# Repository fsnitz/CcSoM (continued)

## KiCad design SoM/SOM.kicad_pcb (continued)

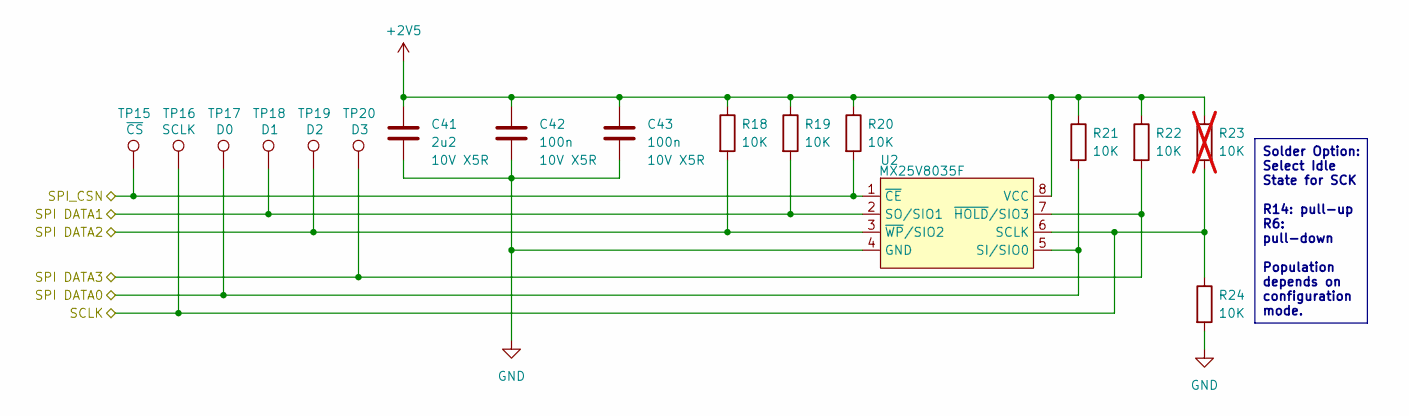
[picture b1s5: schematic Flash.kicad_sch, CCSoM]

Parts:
C41: 2u2; C_0402_1005Metric; Voltage/Precision 10V X5R; Mouser Part Number GRM155Z71A225KE44D
C42, C43: 100n; C_0402_1005Metric; Voltage/Precision 10V X5R; Mouser Part Number GRM155R71C104KA88J
R18, R19, R20, R21, R22, R24: 10K; R_0402_1005Metric; Mouser Part Number MCS0402MC1002FE000
R23: 10K; R_0402_1005Metric; Mouser Part Number 71-CRCW0201-10K; not fitted
TP15: ~{CS}; TestPoint_Pad_D1.0mm
TP16: SCLK; TestPoint_Pad_D1.0mm
TP17: D0; TestPoint_Pad_D1.0mm
TP18: D1; TestPoint_Pad_D1.0mm
TP19: D2; TestPoint_Pad_D1.0mm
TP20: D3; TestPoint_Pad_D1.0mm
U2: MX25V8035F; SOP-8(150_200MIL); Mouser Part Number MX25V8035FM2I

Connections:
+2V5: C41.1, C42.1, C43.1, R18.1, R19.1, R20.1, R21.1, R22.1, R23.1, U2.8 (VCC); also elsewhere on the board
/FPGA_Top_Module/Flash/SCLK: R23.2, R24.1, TP16.1, U2.6 (SCLK); also elsewhere on the board
/FPGA_Top_Module/Flash/SPI DATA0: R21.2, TP17.1, U2.5 (SI/SIO0); also elsewhere on the board
/FPGA_Top_Module/Flash/SPI DATA1: R19.2, TP18.1, U2.2 (SO/SIO1); also elsewhere on the board
/FPGA_Top_Module/Flash/SPI DATA2: R18.2, TP19.1, U2.3 (~WP/SIO2); also elsewhere on the board
/FPGA_Top_Module/Flash/SPI DATA3: R22.2, TP20.1, U2.7 (~HOLD/SIO3); also elsewhere on the board
/FPGA_Top_Module/Flash/SPI_CSN: R20.2, TP15.1, U2.1 (~CE); also elsewhere on the board
GND: C41.2, C42.2, C43.2, R24.2, U2.4 (GND); also elsewhere on the board

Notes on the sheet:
Solder Option: Select Idle State for SCK R14: pull-up R6: pull-down Population depends on configuration mode.

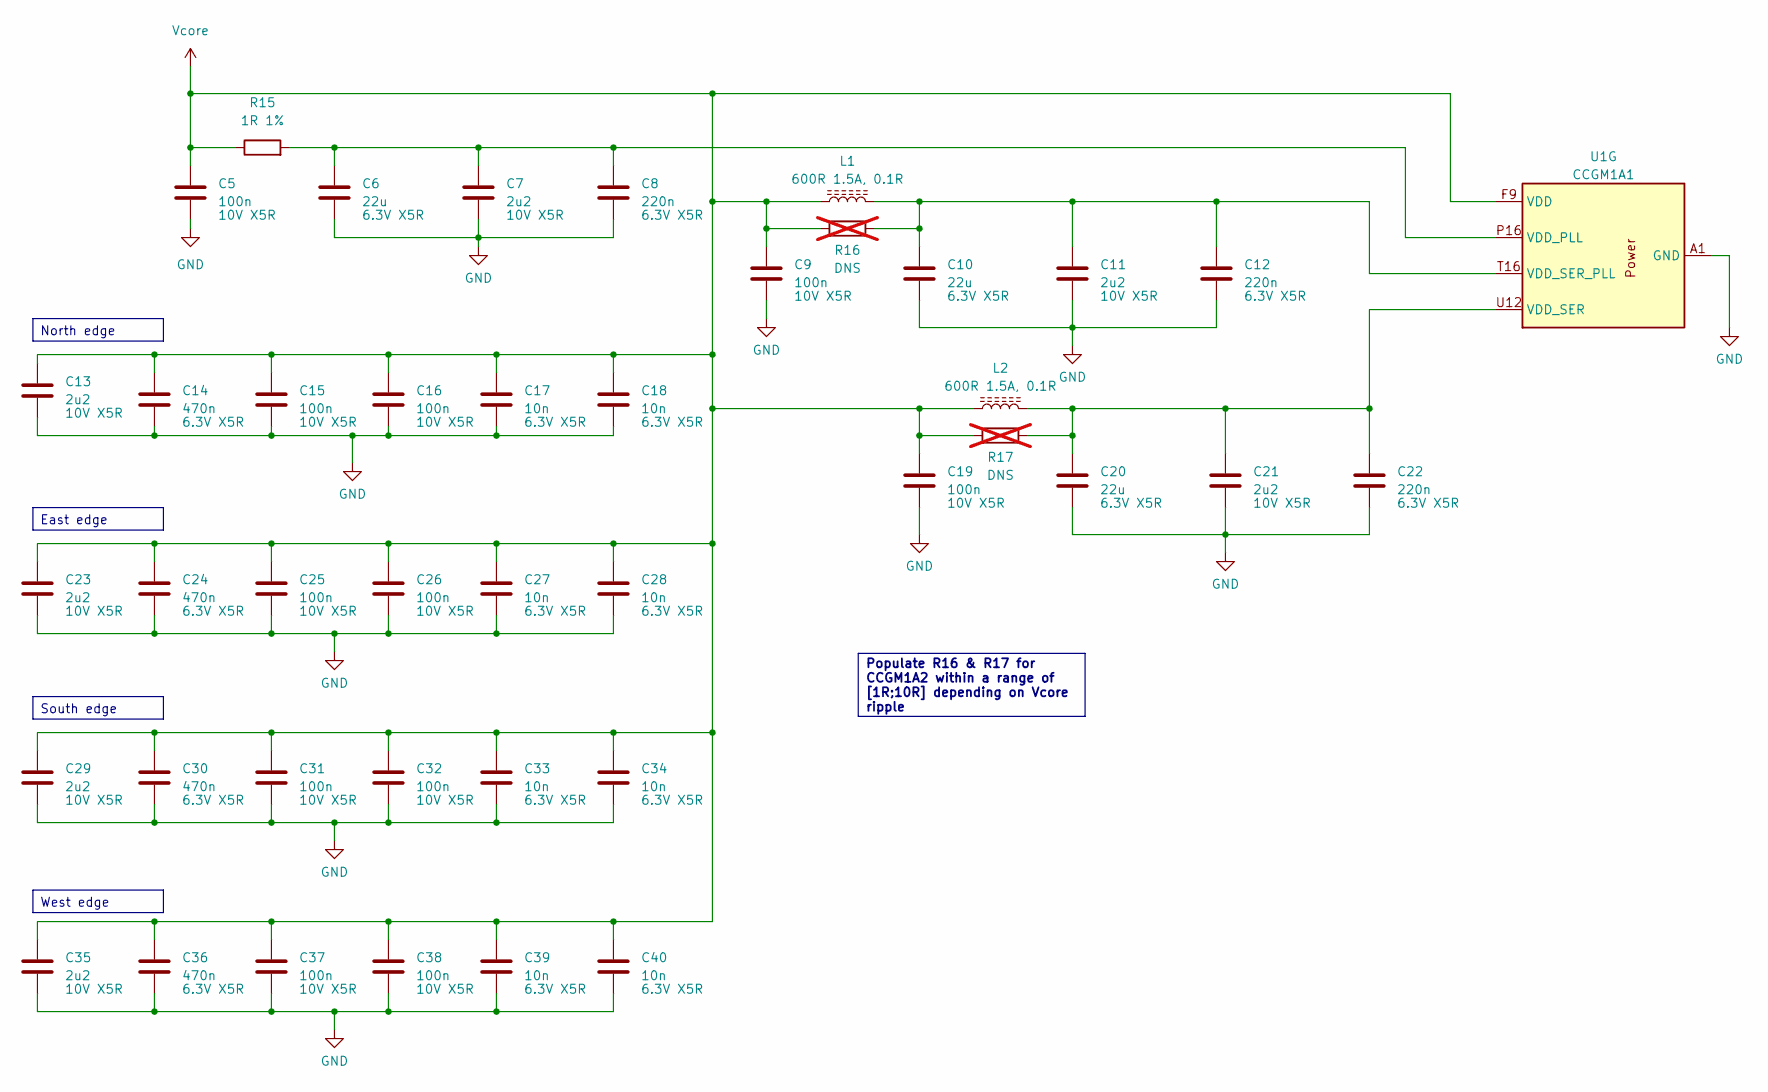
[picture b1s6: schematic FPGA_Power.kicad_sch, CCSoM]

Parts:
C5, C9, C15, C16, C19, C25, C26, C31, C32, C37, C38: 100n; C_0402_1005Metric; Voltage/Precision 10V X5R; Mouser Part Number GRM155R71C104KA88J
C6, C10, C20: 22u; C_0603_1608Metric; Voltage/Precision 6.3V X5R; Mouser Part Number GRM188C61C226ME01W
C7, C11, C13, C21, C23, C29, C35: 2u2; C_0402_1005Metric; Voltage/Precision 10V X5R; Mouser Part Number GRM155Z71A225KE44D
C8, C12, C22: 220n; C_0402_1005Metric; Voltage/Precision 6.3V X5R; Mouser Part Number GRM155R71C224KA12D
C14, C24, C30, C36: 470n; C_0402_1005Metric; Voltage/Precision 6.3V X5R; Mouser Part Number GRT155C81C474KE01D
C17, C18, C27, C28, C33, C34, C39, C40: 10n; C_0402_1005Metric; Voltage/Precision 6.3V X5R; Mouser Part Number GRM155R71C103KA01D
L1, L2: 600R 1.5A, 0.1R; C_0603_1608Metric; Mouser Part Number 74269262601
R15: 1R 1%; R_0402_1005Metric; Mouser Part Number CRCW04021R00FKEDHP
R16, R17: DNS; R_0402_1005Metric; Mouser Part Number 71-CRCW020133R0FNED; not fitted
U1: CCGM1A1; BGA-324_15.0x15.0mm_Layout18x18_P0.8mm_Ball0.45mm_Pad0.4mm_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; Mouser Part Number CCGM1A1-BGA324

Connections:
GND: C5.2, C6.2, C7.2, C8.2, C9.2, C10.2, C11.2, C12.2, C13.2, C14.2, C15.2, C16.2, C17.2, C18.2, C19.2, C20.2, C21.2, C22.2, C23.2, C24.2, C25.2, C26.2, C27.2, C28.2, C29.2, C30.2, C31.2, C32.2, C33.2, C34.2, C35.2, C36.2, C37.2, C38.2, C39.2, C40.2, U1.A1 (GND), U1.A7 (GND), U1.A10 (GND), U1.A13 (GND), U1.A18 (GND), U1.B16 (GND), U1.C1 (GND), U1.E5 (GND), U1.E7 (GND), U1.E9 (GND), U1.E11 (GND), U1.E13 (GND), U1.E18 (GND), U1.F1 (GND), U1.F6 (GND), U1.F8 (GND), U1.F10 (GND), U1.F12 (GND), U1.F14 (GND), U1.G5 (GND), U1.G7 (GND), U1.G9 (GND), U1.G11 (GND), U1.G13 (GND), U1.H6 (GND), U1.H8 (GND), U1.H10 (GND), U1.H12 (GND), U1.H14 (GND), U1.H18 (GND), U1.J1 (GND), U1.J5 (GND), U1.J7 (GND), U1.J9 (GND), U1.J11 (GND), U1.J13 (GND), U1.K6 (GND), U1.K8 (GND), U1.K10 (GND), U1.K12 (GND), U1.K14 (GND), U1.L5 (GND), U1.L7 (GND), U1.L9 (GND), U1.L11 (GND), U1.L13 (GND), U1.L18 (GND), U1.M1 (GND), U1.M6 (GND), U1.M8 (GND), U1.M10 (GND), U1.M12 (GND), U1.M16 (GND), U1.N7 (GND), U1.N9 (GND), U1.N12 (GND), U1.N17 (GND), U1.P4 (GND), U1.P7 (GND), U1.P9 (GND), U1.R12 (GND), U1.R16 (GND), U1.T4 (GND), U1.T11 (GND), U1.T17 (GND), U1.U15 (GND), U1.V1 (GND), U1.V6 (GND), U1.V9 (GND), U1.V18 (GND); also elsewhere on the board
unnamed: C20.1, C21.1, C22.1, L2.2, R17.1, U1.U12 (VDD_SER), U1.V17 (VDD_SER)
unnamed: C6.1, C7.1, C8.1, R15.2, U1.P16 (VDD_PLL)
unnamed: C10.1, C11.1, C12.1, L1.2, R16.1, U1.T16 (VDD_SER_PLL)
Vcore: C5.1, C9.1, C13.1, C14.1, C15.1, C16.1, C17.1, C18.1, C19.1, C23.1, C24.1, C25.1, C26.1, C27.1, C28.1, C29.1, C30.1, C31.1, C32.1, C33.1, C34.1, C35.1, C36.1, C37.1, C38.1, C39.1, C40.1, L1.1, L2.1, R15.1, R16.2, R17.2, U1.F9 (VDD), U1.G6 (VDD), U1.G8 (VDD), U1.G10 (VDD), U1.G12 (VDD), U1.H7 (VDD), U1.H9 (VDD), U1.H11 (VDD), U1.H13 (VDD), U1.J6 (VDD), U1.J8 (VDD), U1.J10 (VDD), U1.J12 (VDD), U1.K7 (VDD), U1.K9 (VDD), U1.K11 (VDD), U1.K13 (VDD), U1.L6 (VDD), U1.L8 (VDD), U1.L10 (VDD), U1.L12 (VDD), U1.M7 (VDD), U1.M9 (VDD), U1.M11 (VDD), U1.M13 (VDD), U1.N6 (VDD), U1.N8 (VDD), U1.N10 (VDD); also elsewhere on the board

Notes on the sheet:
East edge
North edge
South edge
Populate R16 & R17 for CCGM1A2 within a range of [1R;10R] depending on Vcore ripple
West edge

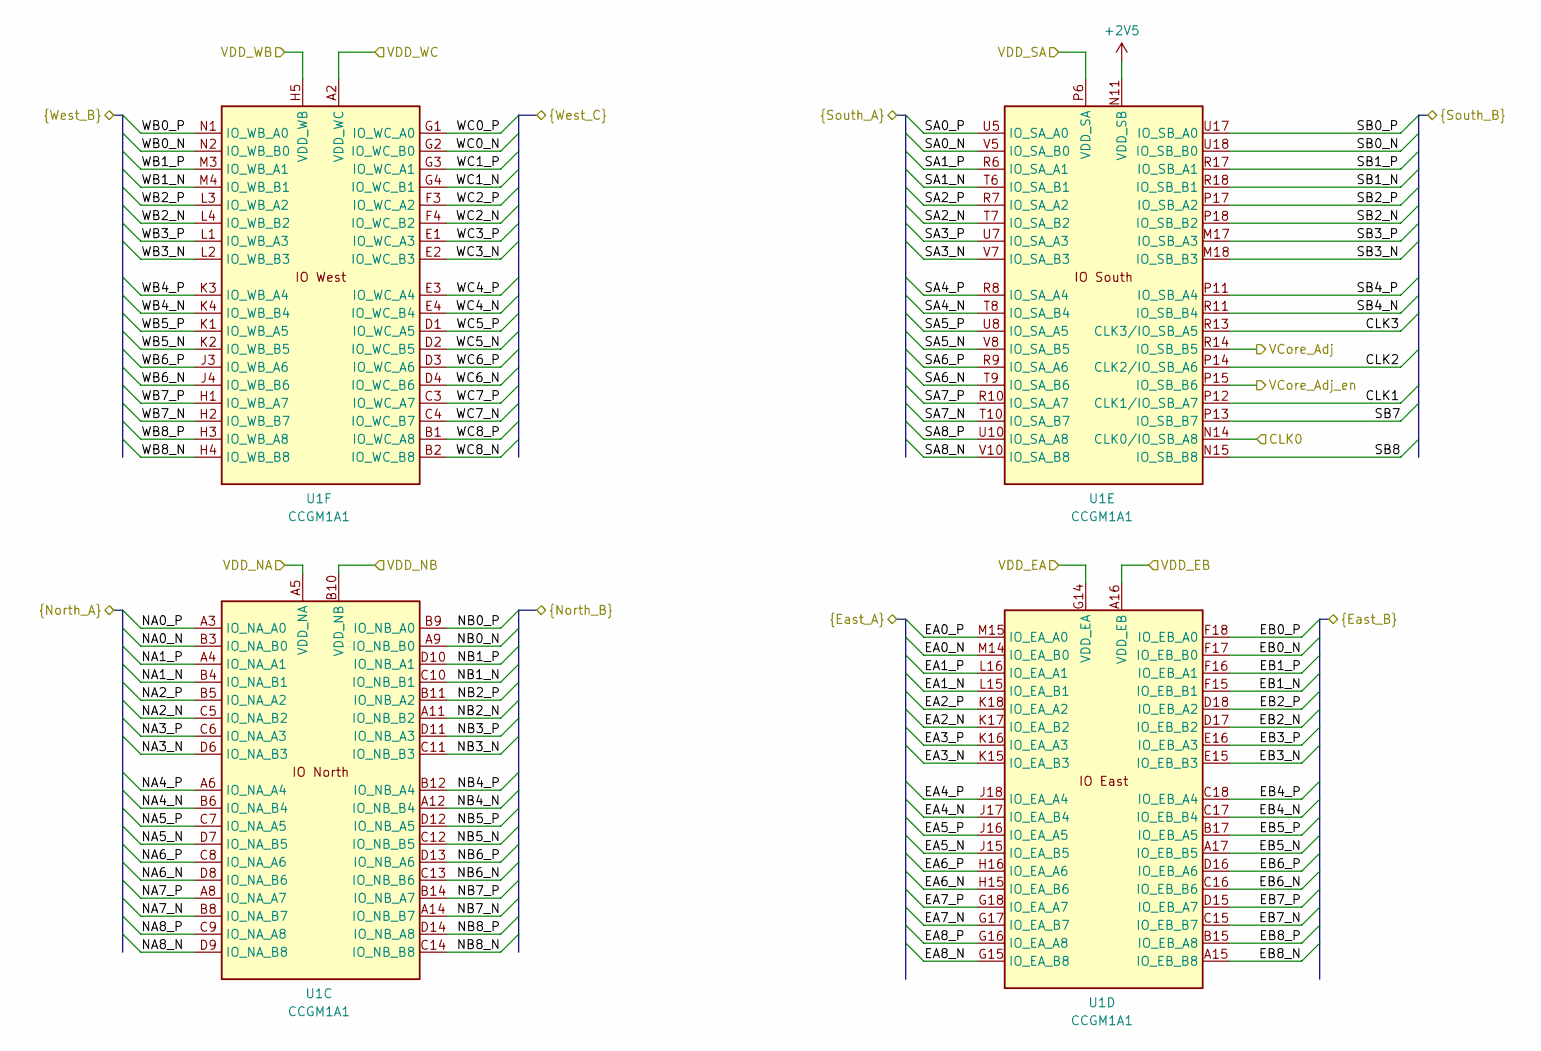
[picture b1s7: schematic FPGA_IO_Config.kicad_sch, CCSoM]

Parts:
U1: CCGM1A1; BGA-324_15.0x15.0mm_Layout18x18_P0.8mm_Ball0.45mm_Pad0.4mm_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; Mouser Part Number CCGM1A1-BGA324

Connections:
+2V5: U1.N11 (VDD_SB), U1.N13 (VDD_SB), U1.N18 (VDD_SB), U1.R15 (VDD_SB), U1.T18 (VDD_SB); also elsewhere on the board
/FPGA_Top_Module/CLK0: U1.N14 (CLK0/IO_SB_A8); also elsewhere on the board
/FPGA_Top_Module/CLK1: U1.P12 (CLK1/IO_SB_A7); also elsewhere on the board
/FPGA_Top_Module/CLK2: U1.P14 (CLK2/IO_SB_A6); also elsewhere on the board
/FPGA_Top_Module/CLK3: U1.R13 (CLK3/IO_SB_A5); also elsewhere on the board
/FPGA_Top_Module/EA0_N: U1.M14 (IO_EA_B0); also elsewhere on the board
/FPGA_Top_Module/EA0_P: U1.M15 (IO_EA_A0); also elsewhere on the board
/FPGA_Top_Module/EA1_N: U1.L15 (IO_EA_B1); also elsewhere on the board
/FPGA_Top_Module/EA1_P: U1.L16 (IO_EA_A1); also elsewhere on the board
/FPGA_Top_Module/EA2_N: U1.K17 (IO_EA_B2); also elsewhere on the board
/FPGA_Top_Module/EA2_P: U1.K18 (IO_EA_A2); also elsewhere on the board
/FPGA_Top_Module/EA3_N: U1.K15 (IO_EA_B3); also elsewhere on the board
/FPGA_Top_Module/EA3_P: U1.K16 (IO_EA_A3); also elsewhere on the board
/FPGA_Top_Module/EA4_N: U1.J17 (IO_EA_B4); also elsewhere on the board
/FPGA_Top_Module/EA4_P: U1.J18 (IO_EA_A4); also elsewhere on the board
/FPGA_Top_Module/EA5_N: U1.J15 (IO_EA_B5); also elsewhere on the board
/FPGA_Top_Module/EA5_P: U1.J16 (IO_EA_A5); also elsewhere on the board
/FPGA_Top_Module/EA6_N: U1.H15 (IO_EA_B6); also elsewhere on the board
/FPGA_Top_Module/EA6_P: U1.H16 (IO_EA_A6); also elsewhere on the board
/FPGA_Top_Module/EA7_N: U1.G17 (IO_EA_B7); also elsewhere on the board
/FPGA_Top_Module/EA7_P: U1.G18 (IO_EA_A7); also elsewhere on the board
/FPGA_Top_Module/EA8_N: U1.G15 (IO_EA_B8); also elsewhere on the board
/FPGA_Top_Module/EA8_P: U1.G16 (IO_EA_A8); also elsewhere on the board
/FPGA_Top_Module/EB0_N: U1.F17 (IO_EB_B0); also elsewhere on the board
/FPGA_Top_Module/EB0_P: U1.F18 (IO_EB_A0); also elsewhere on the board
/FPGA_Top_Module/EB1_N: U1.F15 (IO_EB_B1); also elsewhere on the board
/FPGA_Top_Module/EB1_P: U1.F16 (IO_EB_A1); also elsewhere on the board
/FPGA_Top_Module/EB2_N: U1.D17 (IO_EB_B2); also elsewhere on the board
/FPGA_Top_Module/EB2_P: U1.D18 (IO_EB_A2); also elsewhere on the board
/FPGA_Top_Module/EB3_N: U1.E15 (IO_EB_B3); also elsewhere on the board
/FPGA_Top_Module/EB3_P: U1.E16 (IO_EB_A3); also elsewhere on the board
/FPGA_Top_Module/EB4_N: U1.C17 (IO_EB_B4); also elsewhere on the board
/FPGA_Top_Module/EB4_P: U1.C18 (IO_EB_A4); also elsewhere on the board
/FPGA_Top_Module/EB5_N: U1.A17 (IO_EB_B5); also elsewhere on the board
/FPGA_Top_Module/EB5_P: U1.B17 (IO_EB_A5); also elsewhere on the board
/FPGA_Top_Module/EB6_N: U1.C16 (IO_EB_B6); also elsewhere on the board
/FPGA_Top_Module/EB6_P: U1.D16 (IO_EB_A6); also elsewhere on the board
/FPGA_Top_Module/EB7_N: U1.C15 (IO_EB_B7); also elsewhere on the board
/FPGA_Top_Module/EB7_P: U1.D15 (IO_EB_A7); also elsewhere on the board
/FPGA_Top_Module/EB8_N: U1.A15 (IO_EB_B8); also elsewhere on the board
/FPGA_Top_Module/EB8_P: U1.B15 (IO_EB_A8); also elsewhere on the board
/FPGA_Top_Module/FPGA_IO_Config/VDD_EA: U1.G14 (VDD_EA), U1.H17 (VDD_EA), U1.J14 (VDD_EA), U1.L14 (VDD_EA), U1.L17 (VDD_EA); also elsewhere on the board
/FPGA_Top_Module/FPGA_IO_Config/VDD_EB: U1.A16 (VDD_EB), U1.B18 (VDD_EB), U1.E14 (VDD_EB), U1.E17 (VDD_EB), U1.F13 (VDD_EB); also elsewhere on the board
/FPGA_Top_Module/FPGA_IO_Config/VDD_NA: U1.A5 (VDD_NA), U1.B7 (VDD_NA), U1.E6 (VDD_NA), U1.E8 (VDD_NA), U1.F7 (VDD_NA); also elsewhere on the board
/FPGA_Top_Module/FPGA_IO_Config/VDD_NB: U1.B10 (VDD_NB), U1.B13 (VDD_NB), U1.E10 (VDD_NB), U1.E12 (VDD_NB), U1.F11 (VDD_NB); also elsewhere on the board
/FPGA_Top_Module/FPGA_IO_Config/VDD_SA: U1.P6 (VDD_SA), U1.P8 (VDD_SA), U1.P10 (VDD_SA), U1.U6 (VDD_SA), U1.U9 (VDD_SA); also elsewhere on the board
/FPGA_Top_Module/FPGA_IO_Config/VDD_WB: U1.H5 (VDD_WB), U1.J2 (VDD_WB), U1.K5 (VDD_WB), U1.M2 (VDD_WB), U1.M5 (VDD_WB); also elsewhere on the board
/FPGA_Top_Module/FPGA_IO_Config/VDD_WC: U1.A2 (VDD_WC), U1.C2 (VDD_WC), U1.D5 (VDD_WC), U1.F2 (VDD_WC), U1.F5 (VDD_WC); also elsewhere on the board
/FPGA_Top_Module/NA0_N: U1.B3 (IO_NA_B0); also elsewhere on the board
/FPGA_Top_Module/NA0_P: U1.A3 (IO_NA_A0); also elsewhere on the board
/FPGA_Top_Module/NA1_N: U1.B4 (IO_NA_B1); also elsewhere on the board
/FPGA_Top_Module/NA1_P: U1.A4 (IO_NA_A1); also elsewhere on the board
/FPGA_Top_Module/NA2_N: U1.C5 (IO_NA_B2); also elsewhere on the board
/FPGA_Top_Module/NA2_P: U1.B5 (IO_NA_A2); also elsewhere on the board
/FPGA_Top_Module/NA3_N: U1.D6 (IO_NA_B3); also elsewhere on the board
/FPGA_Top_Module/NA3_P: U1.C6 (IO_NA_A3); also elsewhere on the board
/FPGA_Top_Module/NA4_N: U1.B6 (IO_NA_B4); also elsewhere on the board
/FPGA_Top_Module/NA4_P: U1.A6 (IO_NA_A4); also elsewhere on the board
/FPGA_Top_Module/NA5_N: U1.D7 (IO_NA_B5); also elsewhere on the board
/FPGA_Top_Module/NA5_P: U1.C7 (IO_NA_A5); also elsewhere on the board
/FPGA_Top_Module/NA6_N: U1.D8 (IO_NA_B6); also elsewhere on the board
/FPGA_Top_Module/NA6_P: U1.C8 (IO_NA_A6); also elsewhere on the board
/FPGA_Top_Module/NA7_N: U1.B8 (IO_NA_B7); also elsewhere on the board
/FPGA_Top_Module/NA7_P: U1.A8 (IO_NA_A7); also elsewhere on the board
/FPGA_Top_Module/NA8_N: U1.D9 (IO_NA_B8); also elsewhere on the board
/FPGA_Top_Module/NA8_P: U1.C9 (IO_NA_A8); also elsewhere on the board
/FPGA_Top_Module/NB0_N: U1.A9 (IO_NB_B0); also elsewhere on the board
/FPGA_Top_Module/NB0_P: U1.B9 (IO_NB_A0); also elsewhere on the board
/FPGA_Top_Module/NB1_N: U1.C10 (IO_NB_B1); also elsewhere on the board
/FPGA_Top_Module/NB1_P: U1.D10 (IO_NB_A1); also elsewhere on the board
/FPGA_Top_Module/NB2_N: U1.A11 (IO_NB_B2); also elsewhere on the board
/FPGA_Top_Module/NB2_P: U1.B11 (IO_NB_A2); also elsewhere on the board
/FPGA_Top_Module/NB3_N: U1.C11 (IO_NB_B3); also elsewhere on the board
/FPGA_Top_Module/NB3_P: U1.D11 (IO_NB_A3); also elsewhere on the board
/FPGA_Top_Module/NB4_N: U1.A12 (IO_NB_B4); also elsewhere on the board
/FPGA_Top_Module/NB4_P: U1.B12 (IO_NB_A4); also elsewhere on the board
/FPGA_Top_Module/NB5_N: U1.C12 (IO_NB_B5); also elsewhere on the board
/FPGA_Top_Module/NB5_P: U1.D12 (IO_NB_A5); also elsewhere on the board
/FPGA_Top_Module/NB6_N: U1.C13 (IO_NB_B6); also elsewhere on the board
/FPGA_Top_Module/NB6_P: U1.D13 (IO_NB_A6); also elsewhere on the board
/FPGA_Top_Module/NB7_N: U1.A14 (IO_NB_B7); also elsewhere on the board
/FPGA_Top_Module/NB7_P: U1.B14 (IO_NB_A7); also elsewhere on the board
/FPGA_Top_Module/NB8_N: U1.C14 (IO_NB_B8); also elsewhere on the board
/FPGA_Top_Module/NB8_P: U1.D14 (IO_NB_A8); also elsewhere on the board
/FPGA_Top_Module/SA0_N: U1.V5 (IO_SA_B0); also elsewhere on the board
/FPGA_Top_Module/SA0_P: U1.U5 (IO_SA_A0); also elsewhere on the board
/FPGA_Top_Module/SA1_N: U1.T6 (IO_SA_B1); also elsewhere on the board
/FPGA_Top_Module/SA1_P: U1.R6 (IO_SA_A1); also elsewhere on the board
/FPGA_Top_Module/SA2_N: U1.T7 (IO_SA_B2); also elsewhere on the board
/FPGA_Top_Module/SA2_P: U1.R7 (IO_SA_A2); also elsewhere on the board
/FPGA_Top_Module/SA3_N: U1.V7 (IO_SA_B3); also elsewhere on the board
/FPGA_Top_Module/SA3_P: U1.U7 (IO_SA_A3); also elsewhere on the board
/FPGA_Top_Module/SA4_N: U1.T8 (IO_SA_B4); also elsewhere on the board
/FPGA_Top_Module/SA4_P: U1.R8 (IO_SA_A4); also elsewhere on the board
/FPGA_Top_Module/SA5_N: U1.V8 (IO_SA_B5); also elsewhere on the board
/FPGA_Top_Module/SA5_P: U1.U8 (IO_SA_A5); also elsewhere on the board
/FPGA_Top_Module/SA6_N: U1.T9 (IO_SA_B6); also elsewhere on the board
/FPGA_Top_Module/SA6_P: U1.R9 (IO_SA_A6); also elsewhere on the board
/FPGA_Top_Module/SA7_N: U1.T10 (IO_SA_B7); also elsewhere on the board
/FPGA_Top_Module/SA7_P: U1.R10 (IO_SA_A7); also elsewhere on the board
/FPGA_Top_Module/SA8_N: U1.V10 (IO_SA_B8); also elsewhere on the board
/FPGA_Top_Module/SA8_P: U1.U10 (IO_SA_A8); also elsewhere on the board
/FPGA_Top_Module/SB0_N: U1.U18 (IO_SB_B0); also elsewhere on the board
/FPGA_Top_Module/SB0_P: U1.U17 (IO_SB_A0); also elsewhere on the board
/FPGA_Top_Module/SB1_N: U1.R18 (IO_SB_B1); also elsewhere on the board
/FPGA_Top_Module/SB1_P: U1.R17 (IO_SB_A1); also elsewhere on the board
/FPGA_Top_Module/SB2_N: U1.P18 (IO_SB_B2); also elsewhere on the board
/FPGA_Top_Module/SB2_P: U1.P17 (IO_SB_A2); also elsewhere on the board
/FPGA_Top_Module/SB3_N: U1.M18 (IO_SB_B3); also elsewhere on the board
/FPGA_Top_Module/SB3_P: U1.M17 (IO_SB_A3); also elsewhere on the board
/FPGA_Top_Module/SB4_N: U1.R11 (IO_SB_B4); also elsewhere on the board
/FPGA_Top_Module/SB4_P: U1.P11 (IO_SB_A4); also elsewhere on the board
/FPGA_Top_Module/SB7: U1.P13 (IO_SB_B7); also elsewhere on the board
/FPGA_Top_Module/SB8: U1.N15 (IO_SB_B8); also elsewhere on the board
/FPGA_Top_Module/VcAdj: U1.R14 (IO_SB_B5); also elsewhere on the board
/FPGA_Top_Module/WB0_N: U1.N2 (IO_WB_B0); also elsewhere on the board
/FPGA_Top_Module/WB0_P: U1.N1 (IO_WB_A0); also elsewhere on the board
/FPGA_Top_Module/WB1_N: U1.M4 (IO_WB_B1); also elsewhere on the board
/FPGA_Top_Module/WB1_P: U1.M3 (IO_WB_A1); also elsewhere on the board
/FPGA_Top_Module/WB2_N: U1.L4 (IO_WB_B2); also elsewhere on the board
/FPGA_Top_Module/WB2_P: U1.L3 (IO_WB_A2); also elsewhere on the board
/FPGA_Top_Module/WB3_N: U1.L2 (IO_WB_B3); also elsewhere on the board
/FPGA_Top_Module/WB3_P: U1.L1 (IO_WB_A3); also elsewhere on the board
/FPGA_Top_Module/WB4_N: U1.K4 (IO_WB_B4); also elsewhere on the board
/FPGA_Top_Module/WB4_P: U1.K3 (IO_WB_A4); also elsewhere on the board
/FPGA_Top_Module/WB5_N: U1.K2 (IO_WB_B5); also elsewhere on the board
/FPGA_Top_Module/WB5_P: U1.K1 (IO_WB_A5); also elsewhere on the board
/FPGA_Top_Module/WB6_N: U1.J4 (IO_WB_B6); also elsewhere on the board
/FPGA_Top_Module/WB6_P: U1.J3 (IO_WB_A6); also elsewhere on the board
/FPGA_Top_Module/WB7_N: U1.H2 (IO_WB_B7); also elsewhere on the board
/FPGA_Top_Module/WB7_P: U1.H1 (IO_WB_A7); also elsewhere on the board
/FPGA_Top_Module/WB8_N: U1.H4 (IO_WB_B8); also elsewhere on the board
/FPGA_Top_Module/WB8_P: U1.H3 (IO_WB_A8); also elsewhere on the board
/FPGA_Top_Module/WC0_N: U1.G2 (IO_WC_B0); also elsewhere on the board
/FPGA_Top_Module/WC0_P: U1.G1 (IO_WC_A0); also elsewhere on the board
/FPGA_Top_Module/WC1_N: U1.G4 (IO_WC_B1); also elsewhere on the board
/FPGA_Top_Module/WC1_P: U1.G3 (IO_WC_A1); also elsewhere on the board
/FPGA_Top_Module/WC2_N: U1.F4 (IO_WC_B2); also elsewhere on the board
/FPGA_Top_Module/WC2_P: U1.F3 (IO_WC_A2); also elsewhere on the board
/FPGA_Top_Module/WC3_N: U1.E2 (IO_WC_B3); also elsewhere on the board
/FPGA_Top_Module/WC3_P: U1.E1 (IO_WC_A3); also elsewhere on the board
/FPGA_Top_Module/WC4_N: U1.E4 (IO_WC_B4); also elsewhere on the board
/FPGA_Top_Module/WC4_P: U1.E3 (IO_WC_A4); also elsewhere on the board
/FPGA_Top_Module/WC5_N: U1.D2 (IO_WC_B5); also elsewhere on the board
/FPGA_Top_Module/WC5_P: U1.D1 (IO_WC_A5); also elsewhere on the board
/FPGA_Top_Module/WC6_N: U1.D4 (IO_WC_B6); also elsewhere on the board
/FPGA_Top_Module/WC6_P: U1.D3 (IO_WC_A6); also elsewhere on the board
/FPGA_Top_Module/WC7_N: U1.C4 (IO_WC_B7); also elsewhere on the board
/FPGA_Top_Module/WC7_P: U1.C3 (IO_WC_A7); also elsewhere on the board
/FPGA_Top_Module/WC8_N: U1.B2 (IO_WC_B8); also elsewhere on the board
/FPGA_Top_Module/WC8_P: U1.B1 (IO_WC_A8); also elsewhere on the board
/FPGA_Top_Module/~VcAen: U1.P15 (IO_SB_B6); also elsewhere on the board

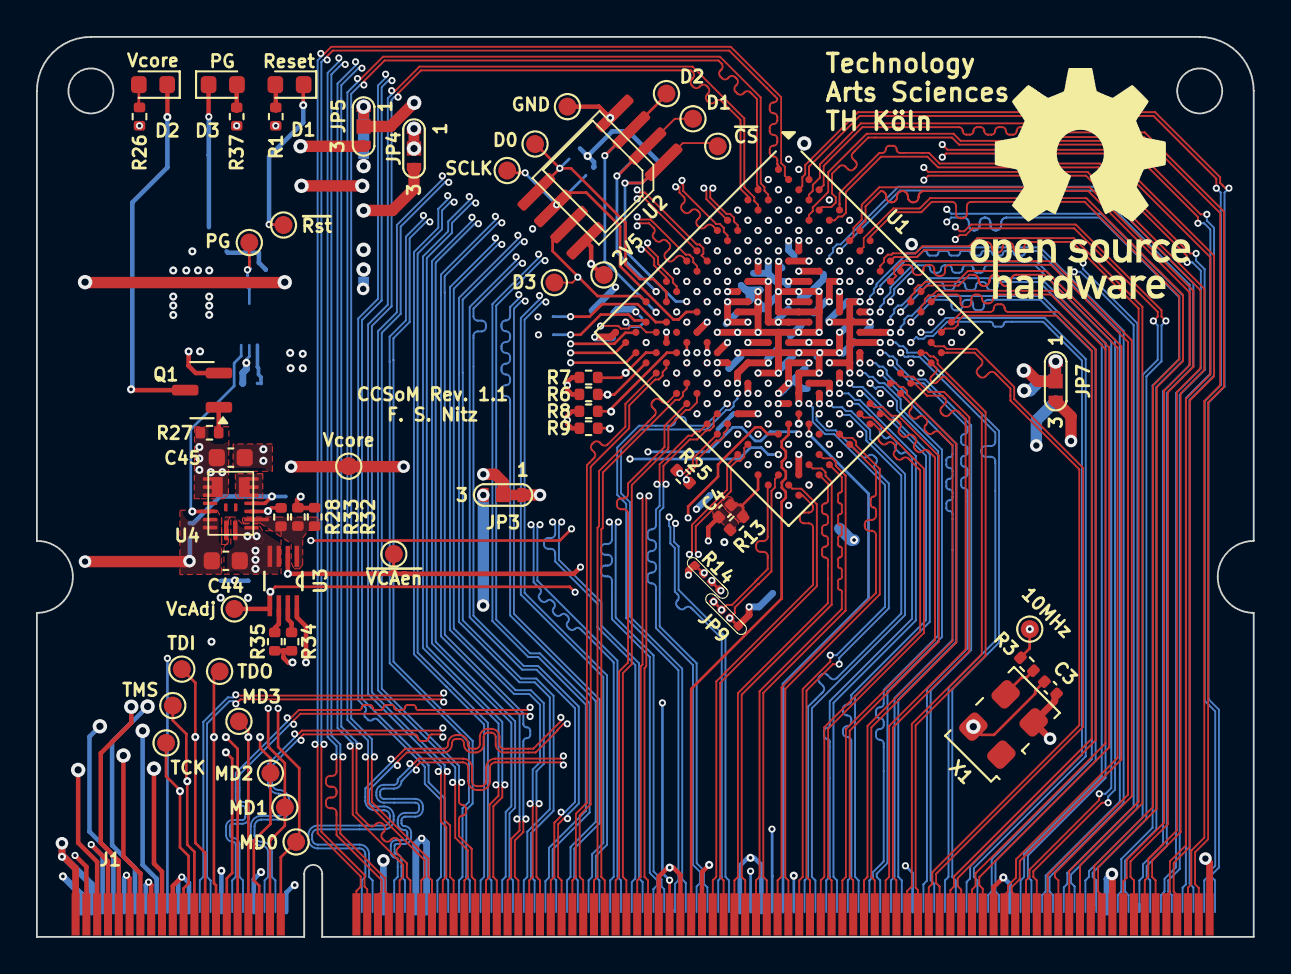
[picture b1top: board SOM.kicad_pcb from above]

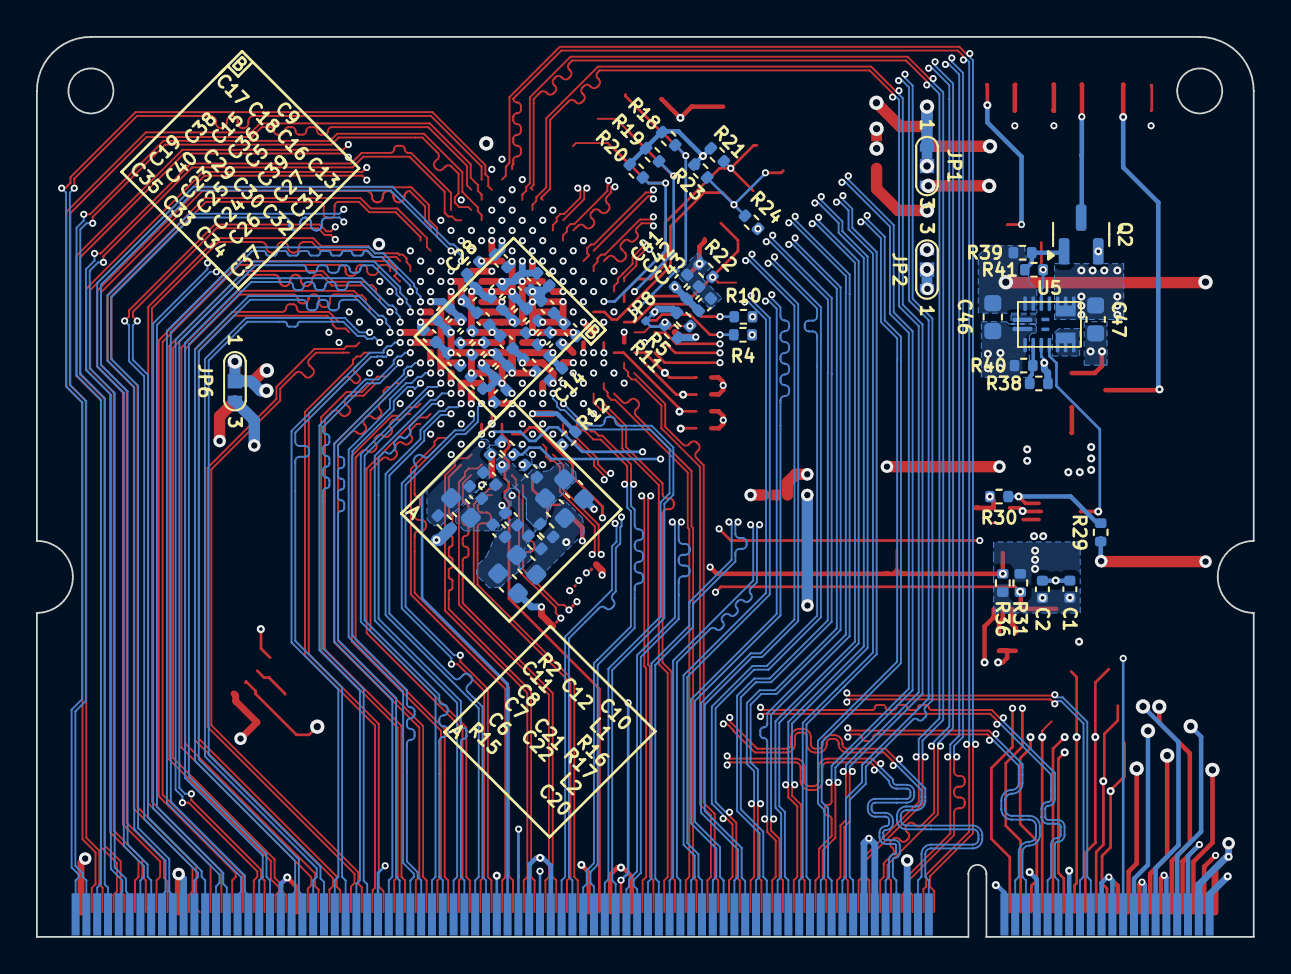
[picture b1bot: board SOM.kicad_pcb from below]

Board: 6 copper layers, 67.6 x 50.0 mm, 135 parts (75 on the bottom side), 212 nets.

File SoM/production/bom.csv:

Designator,Footprint,Quantity,Value,LCSC Part #
"C1, C11, C13, C21, C23, C29, C35, C41, C7",0402,9,2u2,
"C10, C20, C44, C45, C46, C47, C6",0603,7,22u,
"C12, C22, C8",0402,3,220n,
"C14, C24, C30, C36",0402,4,470n,
"C15, C16, C19, C2, C25, C26, C3, C31, C32, C37, C38, C4, C42, C43, C5, C9",0402,16,100n,
"C17, C18, C27, C28, C33, C34, C39, C40",0402,8,10n,
D1,0603,1,Orange,
"D2, D3",0603,2,GREEN,
JP9,Diff_pair_solderbridge_closed,1,~,
"L1, L2",0603,2,"600R 1.5A, 0.1R",
"Q1, Q2",SOT-23,2,BC847,
"R1, R12, R13",0402,3,200R,
"R10, R4, R5",0402,3,4K7,
"R11, R18, R19, R2, R20, R21, R22, R23, R24, R27, R31, R36, R41, R6, R7, R8, R9",0402,17,10K,
R14,Diff_pair_solderbridge_closed,1,100R,
R15,0402,1,1R 1%,
"R16, R17",0402,2,DNS,
R25,0402,1,100R,
"R26, R37",0402,2,1K,
R28,0402,1,20K 1%,
R29,0402,1,100K 1%,
R3,0402,1,33R,
R30,0402,1,51K 1%,
R32,0402,1,240K 1%,
R33,0402,1,47K 1%,
R34,0402,1,120K 1%,
R35,0402,1,62K 1%,
R38,0402,1,200K 1%,
R39,0402,1,12K,
R40,0402,1,63K4 1%,
TP21,TestPoint_Pad_D1.0mm,1,Vcore,
TP22,TestPoint_Pad_D1.0mm,1,PG,
U1,BGA-324_15.0x15.0mm_Layout18x18_P0.8mm_Ball0.45mm_Pad0.4mm_NSMD,1,CCGM1A1,
U2,SOP-8(150_200MIL),1,MX25V8035F,
U3,DCU8,1,74LVC2G53,
"U4, U5",QFN18,2,MPM3833C,
X1,5x3.2_Oscillator,1,ECS-5032MV,

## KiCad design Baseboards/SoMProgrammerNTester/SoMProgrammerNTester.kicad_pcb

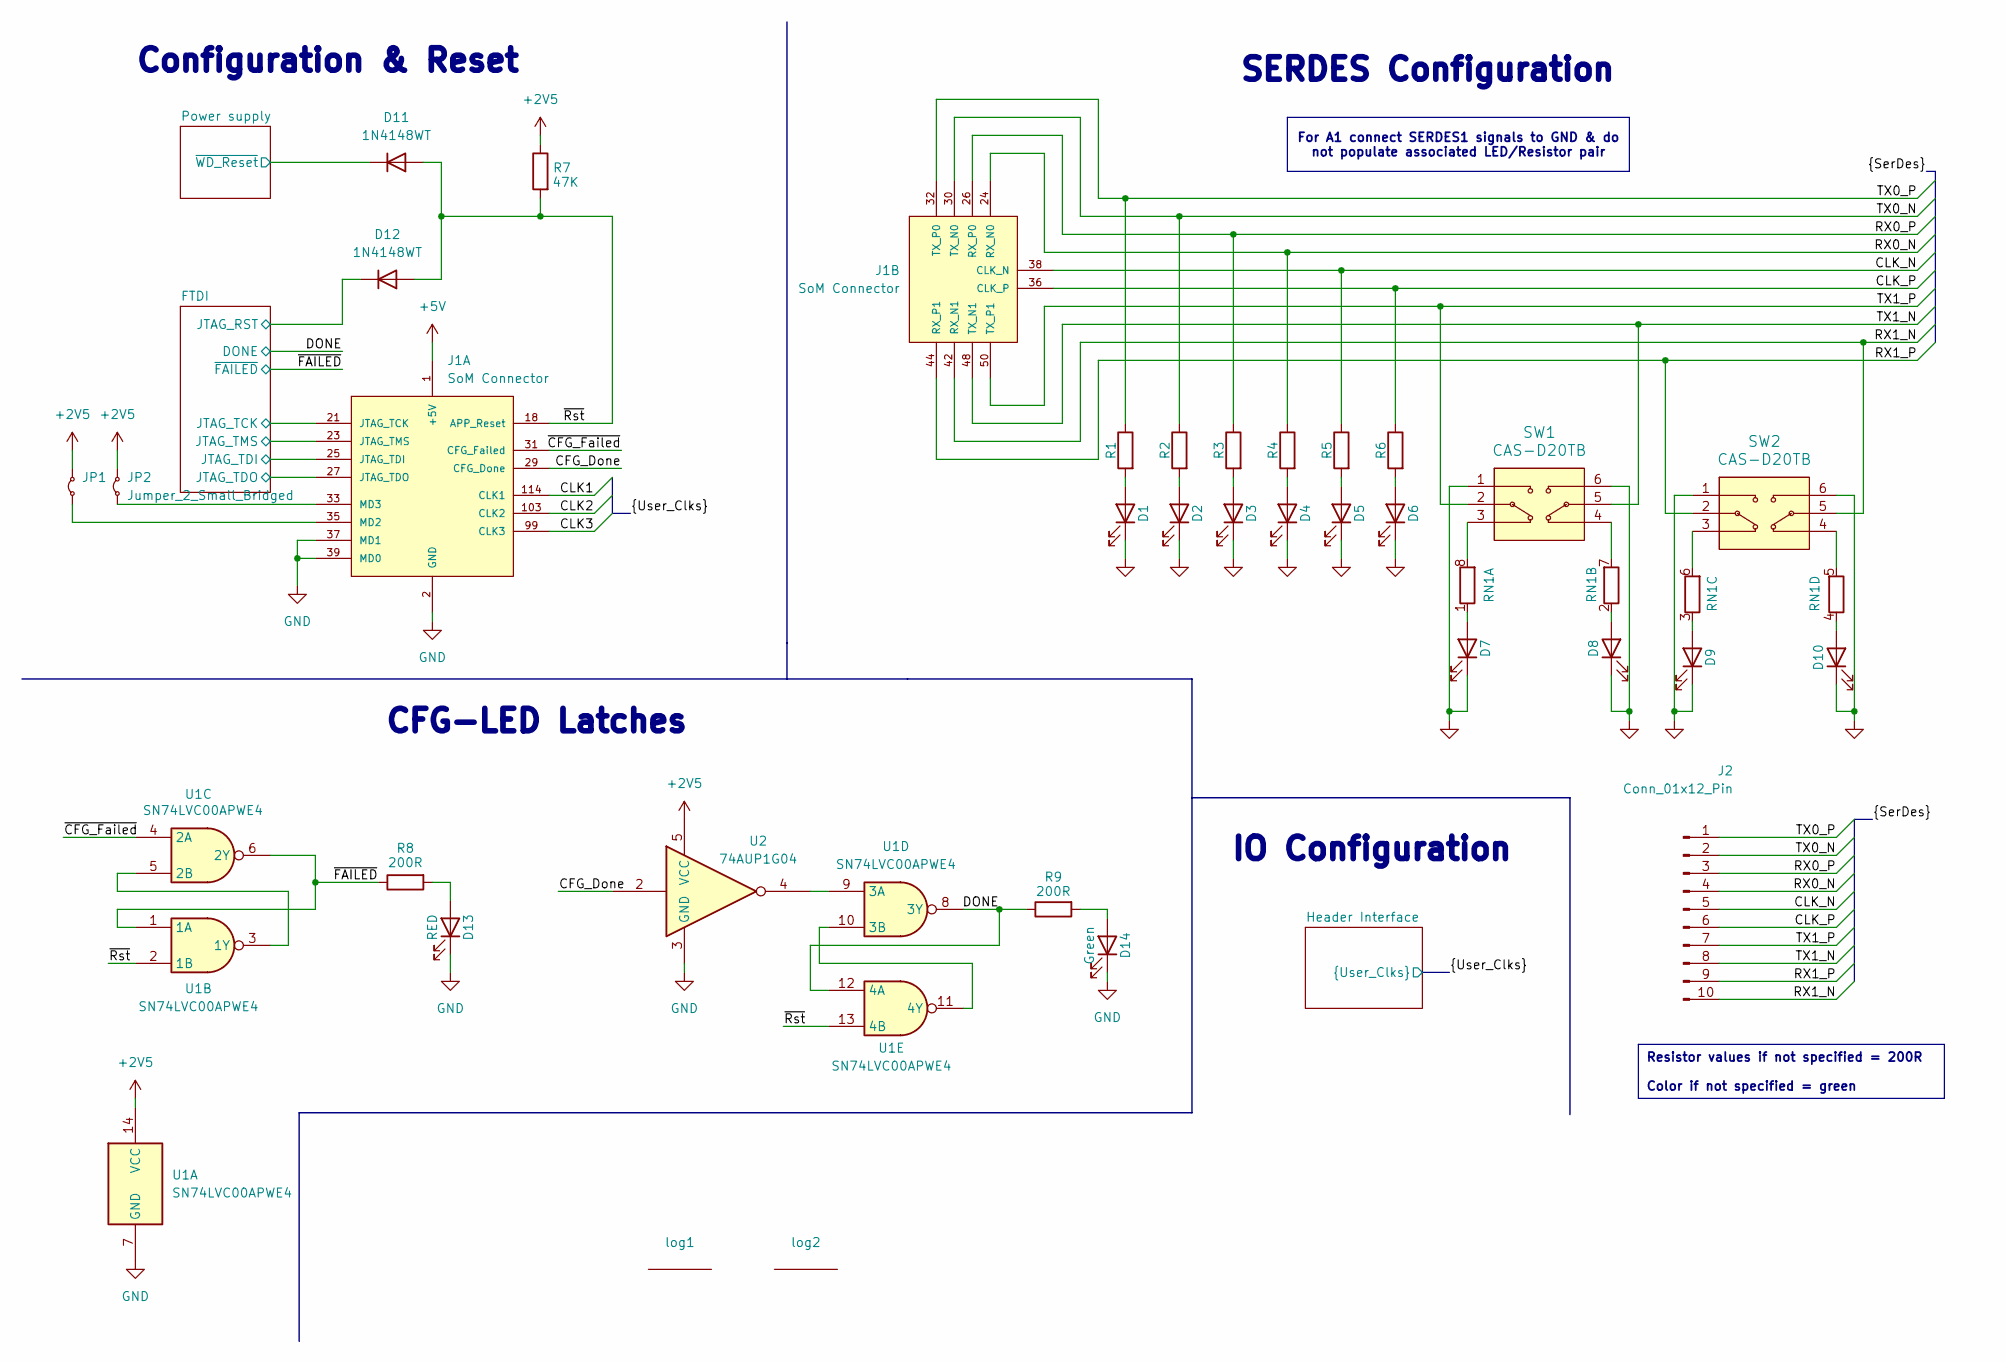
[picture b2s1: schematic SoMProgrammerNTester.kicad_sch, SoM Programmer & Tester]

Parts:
D1, D2, D3, D4, D5, D6, D7, D8, D9, D10, D14: Green; LED_0603_1608Metric; Mouser Part Number 710-150060VS75000
D11, D12: 1N4148WT; D_SOD-523; Mouser Part Number 637-1N4148WT
D13: RED; LED_0603_1608Metric; Mouser Part Number 710-150060SS75000
J1: SoM Connector; SoM_Connector; Mouser Part Number 571-1473005-1
J2: Conn_01x12_Pin; PinHeader_1x10_P2.54mm_Vertical
JP1, JP2: Jumper_2_Small_Bridged; TestPoint_2Pads_Pitch2.54mm_Drill0.8mm
R1, R2, R3, R4, R5, R6, R8, R9: 200R; R_0603_1608Metric; Mouser Part Number 71-CRCW0603200RFKEC
R7: 47K; R_0603_1608Metric; Mouser Part Number 71-CRCW060347K0FKED
RN1: 200R; R_Array_Convex_4x0603; Mouser Part Number 667-EXB-38V201JV
SW1, SW2: CAS-D20TB; CASD20TB; Mouser Part Number 229-CAS-D20TB
U1: SN74LVC00APWE4; TSSOP-14_4.4x5mm_P0.65mm; Mouser Part Number 595-SN74LVC00APWE4
U2: 74AUP1G04; SOT-23-5; Mouser Part Number 595-SN74AUP1G04DBVR
log1: PinguinLogo
log2: OpenHardwareLogo

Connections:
+2V5: JP1.1 (A), JP2.1 (A), R7.1, U1.14 (VCC), U2.5 (VCC); also elsewhere on the board
+5V: J1.1 (+5V), J1.4 (+5V); also elsewhere on the board
/CFG_Done: J1.29 (CFG_Done), U2.2
/CLK1: J1.114 (CLK1); also elsewhere on the board
/CLK2: J1.103 (CLK2); also elsewhere on the board
/CLK3: J1.99 (CLK3); also elsewhere on the board
/CLK_N: J1.38 (CLK_N), J2.5, R5.1
/CLK_P: J1.36 (CLK_P), J2.6, R6.1
/DONE: R9.1, U1.8 (3Y), U1.12 (4A); also elsewhere on the board
/FTDI/JTAG_RST: D12.1 (K); also elsewhere on the board
/FTDI/JTAG_TCK: J1.21 (JTAG_TCK); also elsewhere on the board
/FTDI/JTAG_TDI: J1.25 (JTAG_TDI); also elsewhere on the board
/FTDI/JTAG_TDO: J1.27 (JTAG_TDO); also elsewhere on the board
/FTDI/JTAG_TMS: J1.23 (JTAG_TMS); also elsewhere on the board
/Power supply/~WD_Reset: D11.1 (K); also elsewhere on the board
/RX0_N: J1.24 (RX_N0), J2.4, R4.1
/RX0_P: J1.26 (RX_P0), J2.3, R3.1
/RX1_N: J1.42 (RX_N1), J2.10, SW2.5
/RX1_P: J1.44 (RX_P1), J2.9, SW2.2
/TX0_N: J1.30 (TX_N0), J2.2, R2.1
/TX0_P: J1.32 (TX_P0), J2.1, R1.1
/TX1_N: J1.48 (TX_N1), J2.8, SW1.5
/TX1_P: J1.50 (TX_P1), J2.7, SW1.2
/~CFG_Failed: J1.31 (CFG_Failed), U1.4 (2A)
/~FAILED: R8.1, U1.1 (1A), U1.6 (2Y); also elsewhere on the board
/~Rst: D11.2 (A), D12.2 (A), J1.18 (APP_Reset), R7.2, U1.2 (1B), U1.13 (4B)
GND: D1.1 (K), D2.1 (K), D3.1 (K), D4.1 (K), D5.1 (K), D6.1 (K), D7.1 (K), D8.1 (K), D9.1 (K), D10.1 (K), D13.1 (K), D14.1 (K), J1.2 (GND), J1.3 (GND), J1.6 (GND), J1.7 (GND), J1.10 (GND), J1.11 (GND), J1.14 (GND), J1.15 (GND), J1.19 (GND), J1.20 (GND), J1.22 (GND), J1.28 (GND), J1.34 (GND), J1.37 (MD1), J1.39 (MD0), J1.40 (GND), J1.46 (GND), J1.52 (GND), J1.54 (GND), J1.97 (GND), J1.101 (GND), J1.105 (GND), J1.112 (GND), J1.116 (GND), J1.122 (GND), J1.144 (GND), J1.159 (GND), J1.162 (GND), J1.180 (GND), J1.181 (GND), J1.199 (GND), J1.S1 (SHIELD), J1.S2 (SHIELD__1), SW1.1, SW1.6, SW2.1, SW2.6, U1.7 (GND), U2.3 (GND); also elsewhere on the board
unnamed: D1.2 (A), R1.2
unnamed: D2.2 (A), R2.2
unnamed: D3.2 (A), R3.2
unnamed: D4.2 (A), R4.2
unnamed: D5.2 (A), R5.2
unnamed: D6.2 (A), R6.2
unnamed: D7.2 (A), RN1.1 (R1.1)
unnamed: D8.2 (A), RN1.2 (R2.1)
unnamed: D9.2 (A), RN1.3 (R3.1)
unnamed: D10.2 (A), RN1.4 (R4.1)
unnamed: D13.2 (A), R8.2
unnamed: D14.2 (A), R9.2
unnamed: J1.35 (MD2), JP1.2 (B)
unnamed: J1.33 (MD3), JP2.2 (B)
unnamed: RN1.8 (R1.2), SW1.3
unnamed: RN1.7 (R2.2), SW1.4
unnamed: RN1.6 (R3.2), SW2.3
unnamed: RN1.5 (R4.2), SW2.4
unnamed: U1.3 (1Y), U1.5 (2B)
unnamed: U1.9 (3A), U2.4
unnamed: U1.10 (3B), U1.11 (4Y)

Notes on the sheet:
Resistor values if not specified = 200R Color if not specified = green
For A1 connect SERDES1 signals to GND & do not populate associated LED/Resistor pair
Configuration & Reset
CFG-LED Latches
IO Configuration
SERDES Configuration
